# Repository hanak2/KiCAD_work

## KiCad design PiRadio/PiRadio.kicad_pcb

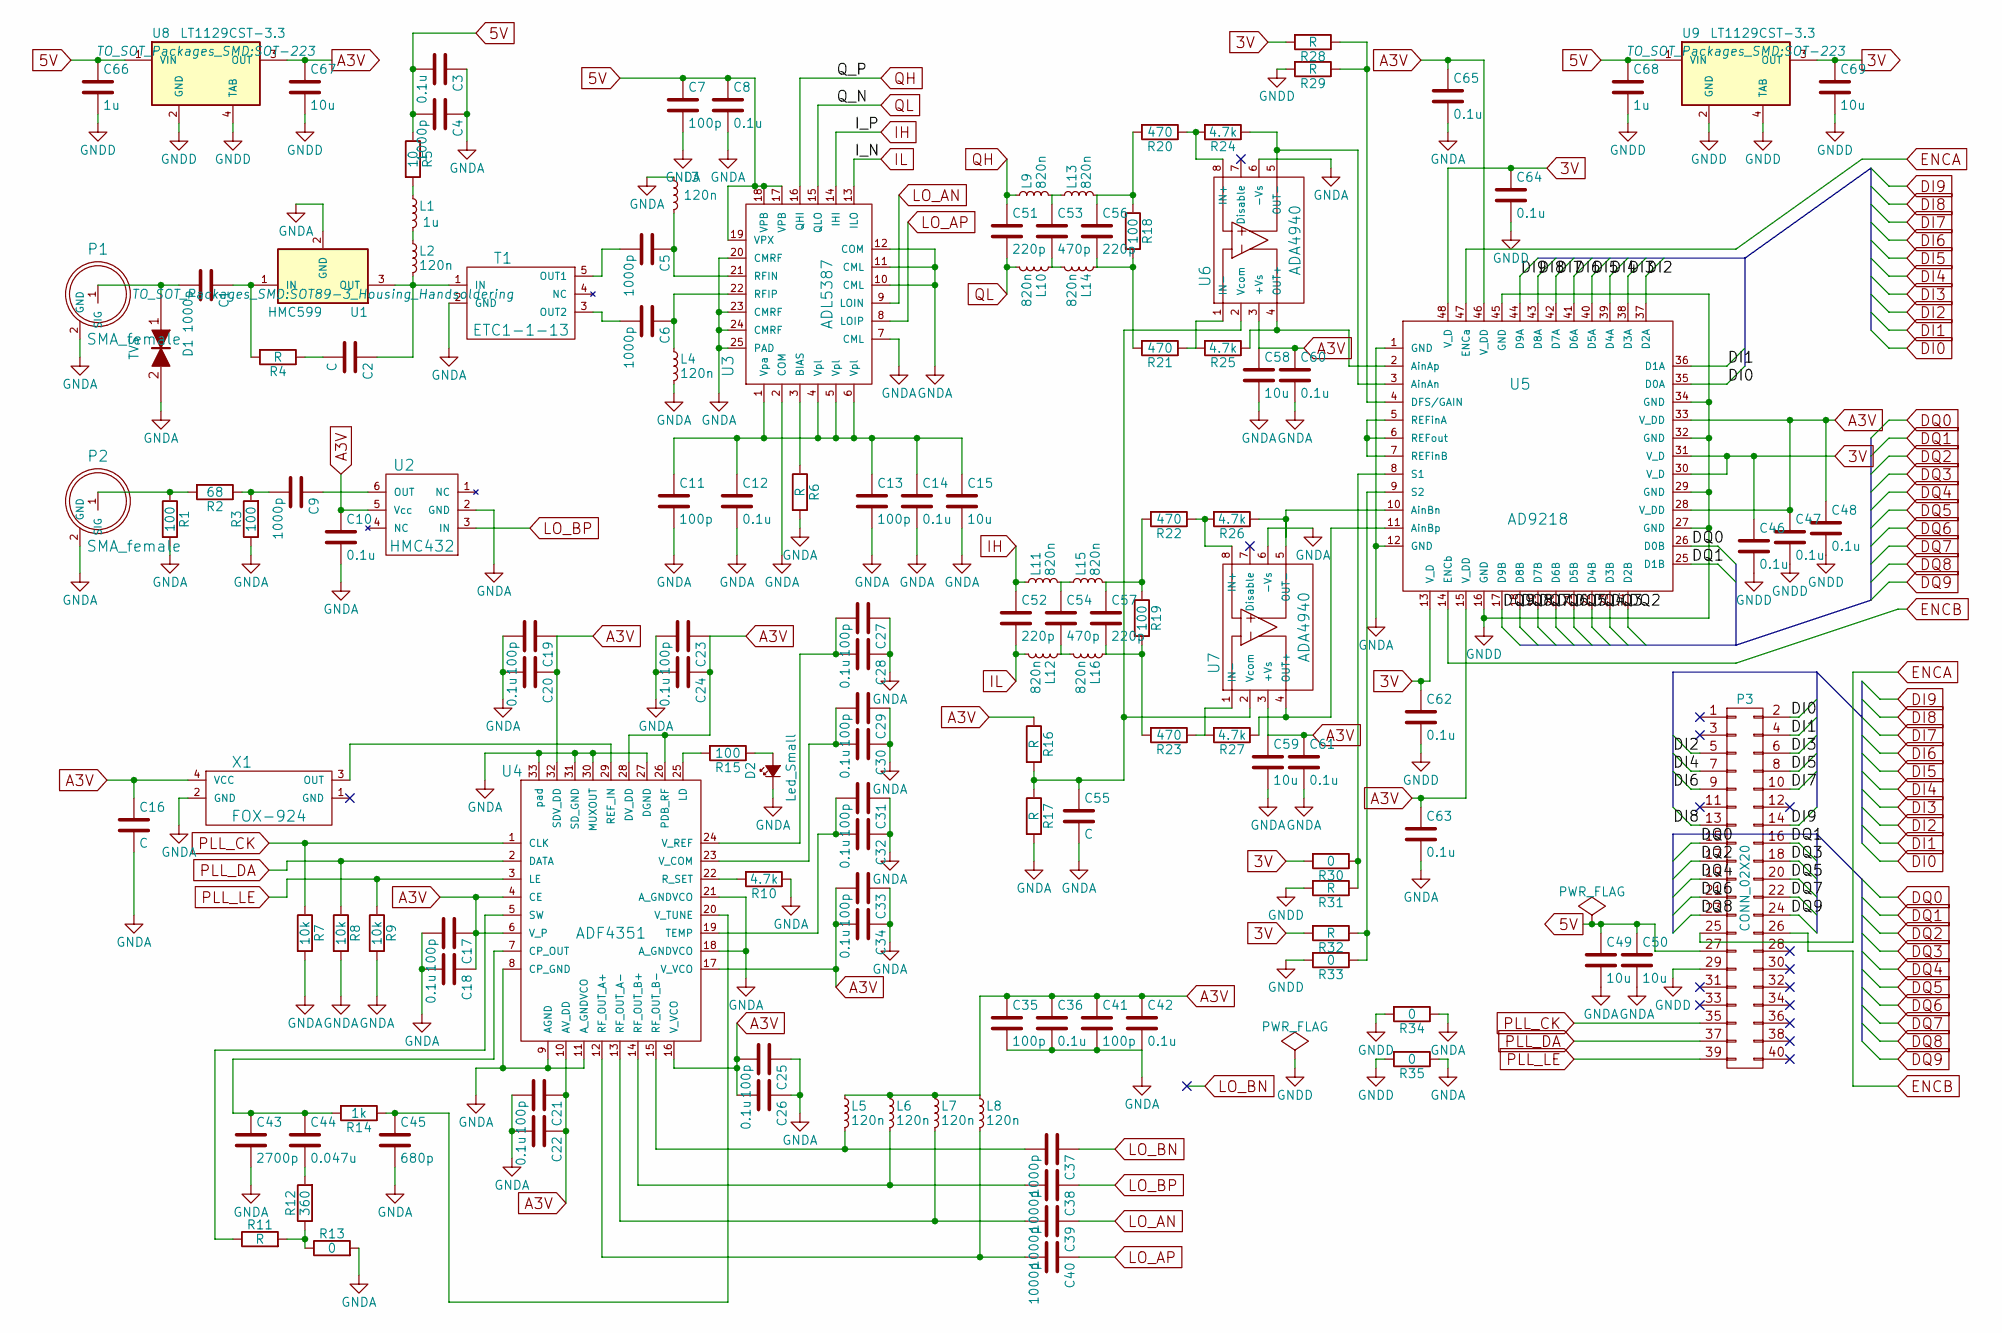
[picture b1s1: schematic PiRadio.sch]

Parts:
C1, C4, C5, C6, C9, C37, C38, C39, C40: 1000p; C_0603
C2, C16, C55: C; C_0603_HandSoldering
C3, C10: 0.1u; C_0603
C7, C11, C13, C17, C19, C21, C23, C25, C27, C29, C31, C33, C35, C41: 100p; C_0603_HandSoldering
C8, C12, C14, C18, C20, C22, C24, C26, C28, C30, C32, C34, C36, C42, C46, C47, C48, C60, C61, C62, C63, C64, C65: 0.1u; C_0603_HandSoldering
C15, C49, C50, C58, C59, C67, C69: 10u; C_0603_HandSoldering
C43: 2700p; C_0603_HandSoldering
C44: 0.047u; C_0603_HandSoldering
C45: 680p; C_0603_HandSoldering
C51, C52, C56, C57: 220p; C_0603
C53, C54: 470p; C_0603
C66, C68: 1u; C_0603_HandSoldering
D1: TVS; C_0603
D2: Led_Small; SMD-1206_Pol
L1: 1u; SMD-1206_Pol
L2, L3, L4, L5, L6, L7, L8: 120n; SMD-1206_Pol
L9, L10, L11, L12, L13, L14, L15, L16: 820n; SMD-1206_Pol
P1, P2: SMA_female; CON_SMA
P3: CONN_02X20; Pin_Header_Straight_2x20
R1, R3, R18, R19: 100; R_0603
R2: 68; R_0603
R4, R6, R11, R16, R17, R28, R29, R31, R32: R; R_0603_HandSoldering
R5: 10; R_0603
R7, R8, R9: 10k; R_0603_HandSoldering
R10: 4.7k; R_0603_HandSoldering
R12: 360; R_0603_HandSoldering
R13, R30, R33, R34, R35: 0; R_0603_HandSoldering
R14: 1k; R_0603_HandSoldering
R15: 100; R_0603_HandSoldering
R20, R21, R22, R23: 470; R_0603
R24, R25, R26, R27: 4.7k; R_0603
T1: ETC1-1-13; NF-Transformer_ETC_1_1_13_HandSoldering
U1: HMC599; SOT89-3_Housing_Handsoldering
U2: HMC432; SOT-26-6_Handsoldering
U3: ADL5387; QFN-24_4x4mm_Pitch0.5mm_SarmalPad
U4: ADF4351; QFN-32-1EP_5x5mm_Pitch0.5mm
U5: AD9218; LQFP-48_7x7mm_Pitch0.5mm
U6, U7: ADA4940; SOIC-8_3.9x4.9mm_Pitch1.27mm
U8, U9: LT1129CST-3.3; SOT-223
X1: FOX-924; FOX924

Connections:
3V: C46.1, C62.1, C64.1, C69.1, R28.2, R30.2, R32.2, U5.13 (V_D), U5.30 (V_D), U5.31 (V_D), U5.48 (V_D), U9.3 (OUT)
5V: C3.2, C4.2, C7.1, C8.1, C49.1, C50.1, C66.1, C68.1, P3.27, R5.1, U3.17 (VPB), U3.18 (VPB), U3.19 (VPX), U8.1 (VIN), U9.1 (VIN)
A3V: C10.1, C16.1, C17.1, C18.1, C19.1, C20.1, C21.1, C22.1, C23.1, C24.1, C25.2, C26.2, C33.2, C34.2, C35.1, C36.1, C41.1, C42.1, C47.1, C48.1, C58.1, C59.1, C60.1, C61.1, C63.1, C65.1, C67.1, L5.1, L6.1, L7.1, L8.1, R16.1, U2.5 (Vcc), U4.4 (CE), U4.6 (V_P), U4.10 (AV_DD), U4.16 (V_VCO), U4.17 (V_VCO), U4.26 (PDB_RF), U4.28 (DV_DD), U4.32 (SDV_DD), U5.15 (V_DD), U5.28 (V_DD), U5.33 (V_DD), U5.46 (V_DD), U6.3 (+Vs), U7.3 (+Vs), U8.3 (OUT), X1.4 (VCC)
DI0: P3.2, U5.35 (D0A)
DI1: P3.4, U5.36 (D1A)
DI2: P3.5, U5.37 (D2A)
DI3: P3.6, U5.38 (D3A)
DI4: P3.7, U5.39 (D4A)
DI5: P3.8, U5.40 (D5A)
DI6: P3.9, U5.41 (D6A)
DI7: P3.10, U5.42 (D7A)
DI8: P3.13, U5.43 (D8A)
DI9: P3.14, U5.44 (D9A)
DQ0: P3.15, U5.26 (D0B)
DQ1: P3.16, U5.25 (D1B)
DQ2: P3.17, U5.24 (D2B)
DQ3: P3.18, U5.23 (D3B)
DQ4: P3.19, U5.22 (D4B)
DQ5: P3.20, U5.21 (D5B)
DQ6: P3.21, U5.20 (D6B)
DQ7: P3.22, U5.19 (D7B)
DQ8: P3.23, U5.18 (D8B)
DQ9: P3.24, U5.17 (D9B)
ENCA: P3.25, U5.47 (ENCa)
ENCB: P3.26, U5.14 (ENCb)
GNDA: C3.1, C4.1, C7.2, C8.2, C10.2, C11.2, C12.2, C13.2, C14.2, C15.2, C16.2, C17.2, C18.2, C19.2, C20.2, C21.2, C22.2, C23.2, C24.2, C25.1, C26.1, C27.1, C28.1, C29.1, C30.1, C31.1, C32.1, C33.1, C34.1, C35.2, C36.2, C41.2, C42.2, C43.2, C45.2, C49.2, C50.2, C55.2, C58.2, C59.2, C60.2, C61.2, C63.2, C65.2, D1.2, D2.1 (K), L3.1, L4.2, P1.2 (GND), P2.2 (GND), R1.2, R3.1, R6.2, R7.2, R8.2, R9.2, R10.1, R13.2, R17.2, R34.1, R35.1, T1.2 (GND), U1.2 (GND), U2.2 (GND), U3.2 (COM), U3.7 (CML), U3.10 (CML), U3.11 (CML), U3.12 (COM), U3.20 (CMRF), U3.23 (CMRF), U3.24 (CMRF), U3.25 (PAD), U4.8 (CP_GND), U4.9 (AGND), U4.11 (A_GNDVCO), U4.18 (A_GNDVCO), U4.21 (A_GNDVCO), U4.27 (DGND), U4.30 (MUXOUT), U4.31 (SD_GND), U4.33 (pad), U5.1 (GND), U5.12 (GND), U6.6 (-Vs), U7.6 (-Vs), X1.2 (GND)
GNDD: C46.2, C47.2, C48.2, C62.2, C64.2, C66.2, C67.2, C68.2, C69.2, P3.29, R29.2, R31.2, R33.2, R34.2, R35.2, U5.16 (GND), U5.27 (GND), U5.29 (GND), U5.32 (GND), U5.34 (GND), U5.45 (GND), U8.2 (GND), U8.4 (TAB), U9.2 (GND), U9.4 (TAB)
IH: C52.1, L11.1, U3.14 (IHI)
IL: C52.2, L12.2, U3.13 (ILO)
LO_AN: C39.1, U3.9 (LOIN)
LO_AP: C40.1, U3.8 (LOIP)
LO_BN: C37.1
LO_BP: C38.1, U2.3 (IN)
unnamed: C1.1, R4.2, U1.1 (IN)
unnamed: C1.2, D1.1, P1.1 (SIG)
unnamed: C2.1, L2.2, T1.1 (IN), U1.3 (OUT)
unnamed: C2.2, R4.1
unnamed: C5.1, L3.2, U3.21 (RFIN)
unnamed: C5.2, T1.5 (OUT1)
unnamed: C6.1, L4.1, U3.22 (RFIP)
unnamed: C6.2, T1.3 (OUT2)
unnamed: C9.1, U2.6 (OUT)
unnamed: C9.2, R2.1, R3.2
unnamed: C11.1, C12.1, C13.1, C14.1, C15.1, U3.1 (Vpa), U3.4 (Vpl), U3.5 (Vpl), U3.6 (Vpl)
unnamed: C27.2, C28.2, U4.24 (V_REF)
unnamed: C29.2, C30.2, U4.23 (V_COM)
unnamed: C31.2, C32.2, U4.19 (TEMP)
unnamed: C37.2, L5.2, U4.15 (RF_OUT_B-)
unnamed: C38.2, L6.2, U4.14 (RF_OUT_B+)
unnamed: C39.2, L7.2, U4.13 (RF_OUT_A-)
unnamed: C40.2, L8.2, U4.12 (RF_OUT_A+)
unnamed: C43.1, C44.1, R14.2, U4.7 (CP_OUT)
unnamed: C44.2, R12.2
unnamed: C45.1, R14.1, U4.20 (V_TUNE)
unnamed: C53.1, L9.2, L13.1
unnamed: C53.2, L10.1, L14.2
unnamed: C54.1, L11.2, L15.1
unnamed: C54.2, L12.1, L16.2
unnamed: C55.1, R16.2, R17.1, U6.2 (Vcom), U7.2 (Vcom)
unnamed: C56.1, L13.2, R18.1, R20.2
unnamed: C56.2, L14.1, R18.2, R21.2
unnamed: C57.1, L15.2, R19.1, R22.2
unnamed: C57.2, L16.1, R19.2, R23.2
unnamed: D2.2 (A), R15.1
unnamed: L1.1, R5.2
unnamed: L1.2, L2.1
unnamed: P2.1 (SIG), R1.1, R2.2
unnamed: R6.1, U3.3 (BIAS)
unnamed: R10.2, U4.22 (R_SET)
unnamed: R11.1, U4.5 (SW)
unnamed: R11.2, R12.1, R13.1
unnamed: R15.2, U4.25 (LD)
unnamed: R20.1, R24.2, U6.8 (IN+)
unnamed: R21.1, R25.2, U6.1 (IN-)
unnamed: R22.1, R26.2, U7.8 (IN+)
unnamed: R23.1, R27.2, U7.1 (IN-)
unnamed: R24.1, U5.3 (AinAn), U6.5 (OUT-)
unnamed: R25.1, U5.2 (AinAp), U6.4 (OUT+)
unnamed: R26.1, U5.10 (AinBn), U7.5 (OUT-)
unnamed: R27.1, U5.11 (AinBp), U7.4 (OUT+)
unnamed: R28.1, R29.1, U5.4 (DFS/GAIN)
unnamed: R30.1, R31.1, U5.8 (S1)
unnamed: R32.1, R33.1, U5.9 (S2)
unnamed: U4.29 (REF_IN), X1.3 (OUT)
unnamed: U5.5 (REFinA), U5.6 (REFout), U5.7 (REFinB)
PLL_CK: P3.35, R7.1, U4.1 (CLK)
PLL_DA: P3.37, R8.1, U4.2 (DATA)
PLL_LE: P3.39, R9.1, U4.3 (LE)
QH: C51.1, L9.1, U3.16 (QHI)
QL: C51.2, L10.2, U3.15 (QLO)

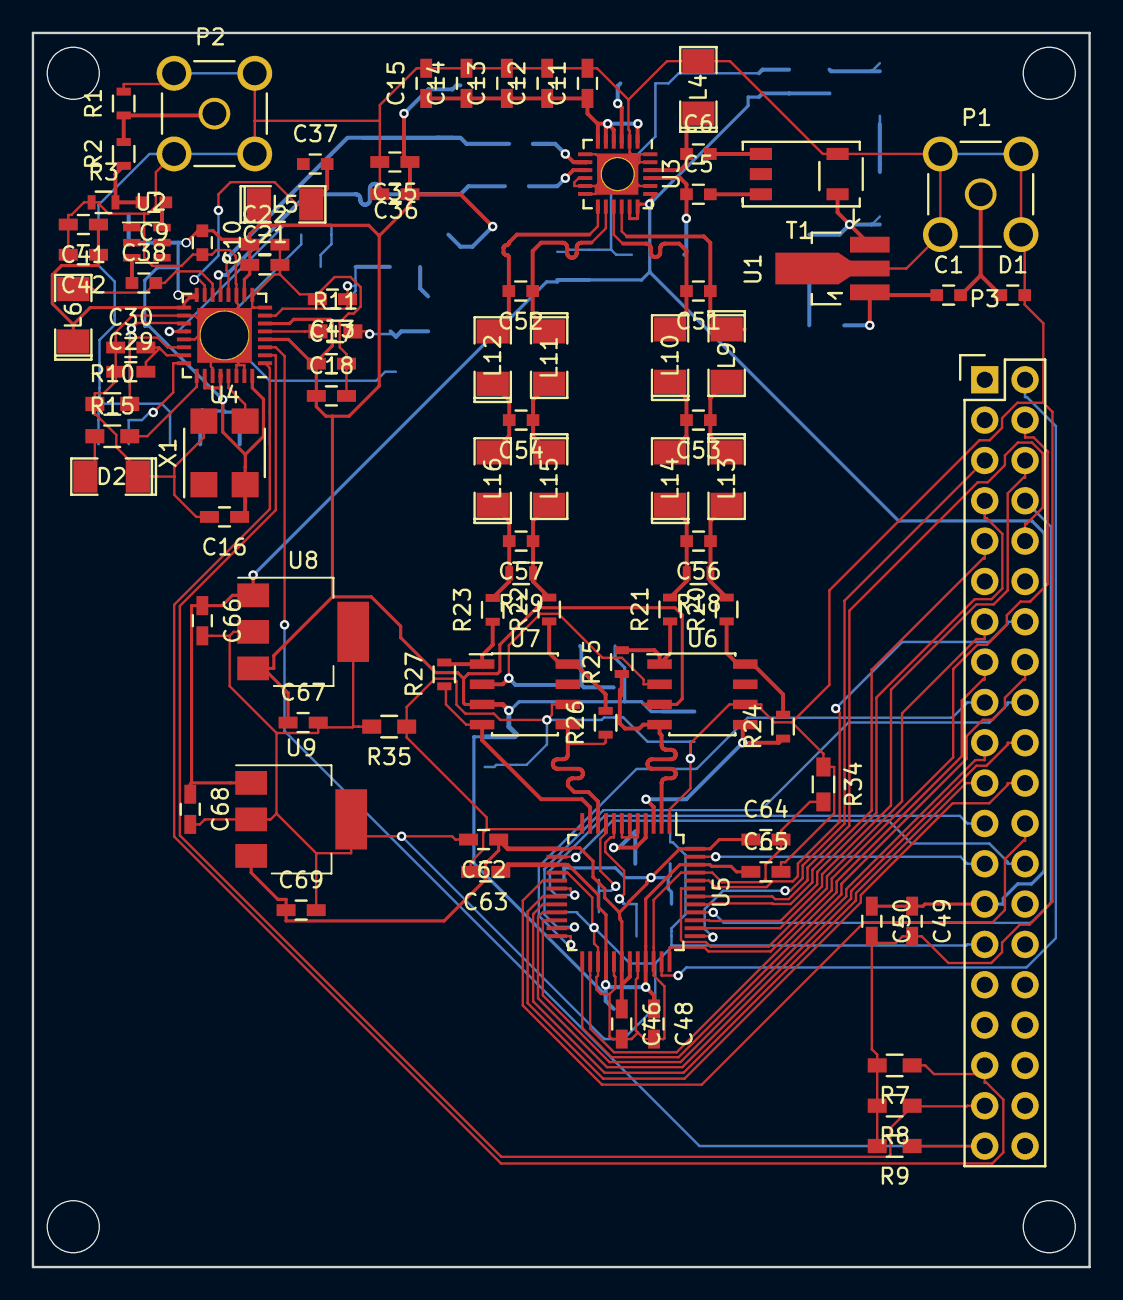
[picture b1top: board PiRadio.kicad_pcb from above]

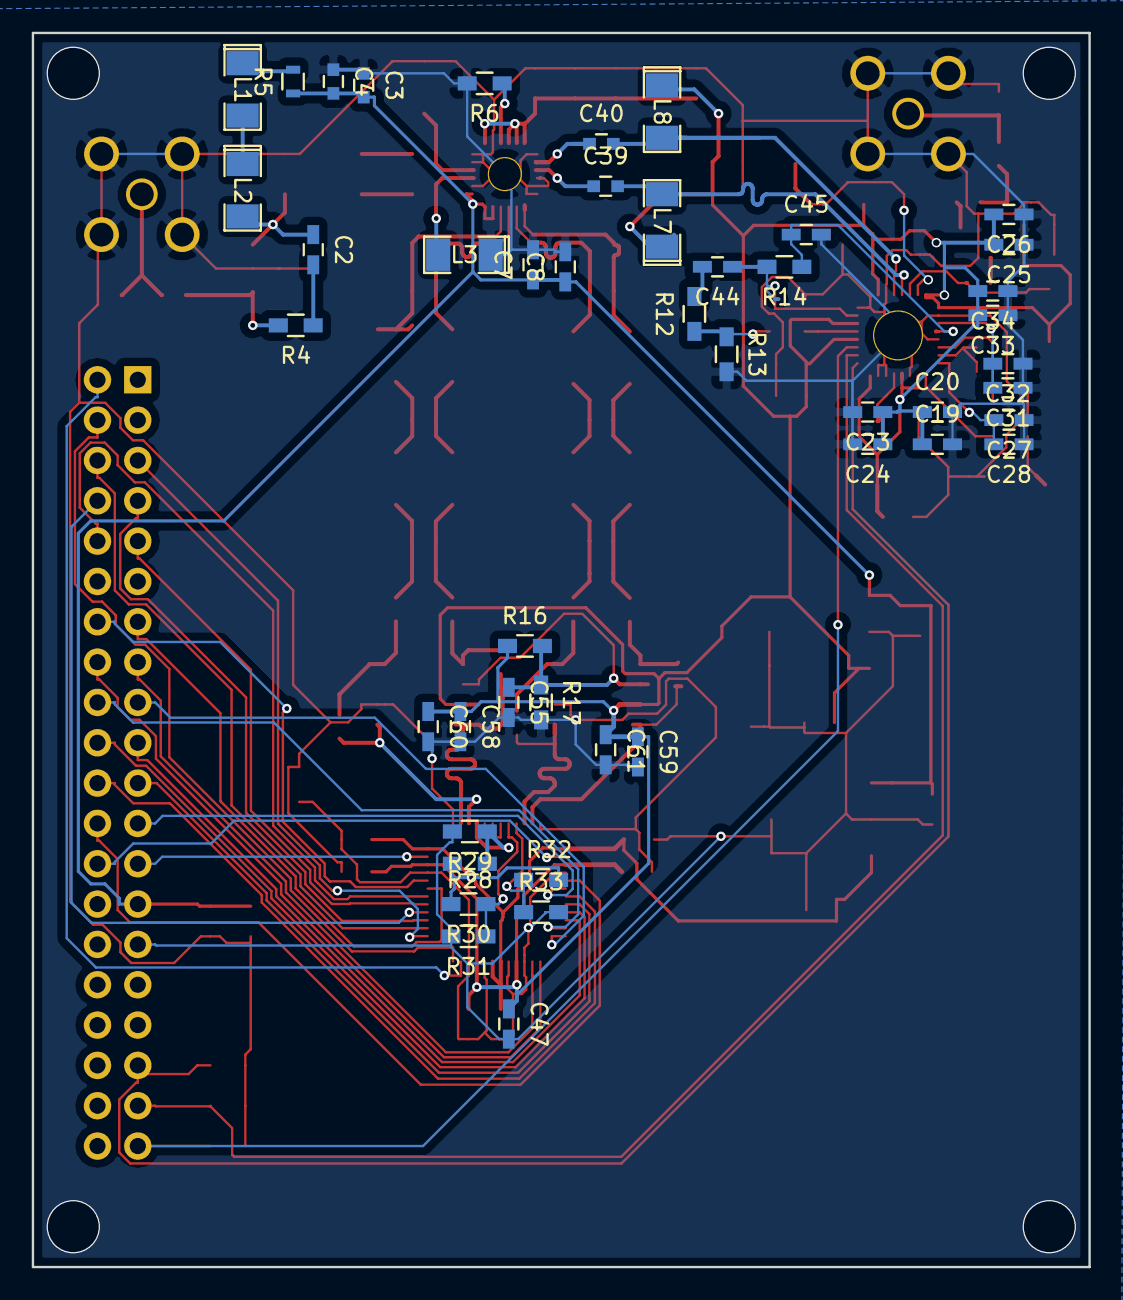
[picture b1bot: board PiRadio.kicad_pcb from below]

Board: 2 copper layers, 66.5 x 77.7 mm, 136 parts (46 on the bottom side), 89 nets.

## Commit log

2016-10-25 initial test
2016-10-25 test mod
2016-12-23 changes compLib & Schem
    add HMC599 & ADL5387
2016-12-24 changes of CompLib and Shem
    add IQ-Dec & PLL
2016-12-24 changes of CompLib & Shem
    add ADcon
2017-01-05 Changes of PCB
    PCB Position Determined
2017-01-05 changes of pcb
    route and patern completed
